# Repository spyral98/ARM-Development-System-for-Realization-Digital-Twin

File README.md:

# ARM-Development-System-to-Support-Digital-Twin-of-Stepper-Motor 
This repository consists of the work conducted for the thesis "ARM Development System to Support Digital Twin of Stepper Motor". It contains all the files necessary for the development of a fully functional system built around an STM32 Cortex-M4 microcontroller, as well as the code for a demo application for it. It also contains the code for a data representation application using Matlab.

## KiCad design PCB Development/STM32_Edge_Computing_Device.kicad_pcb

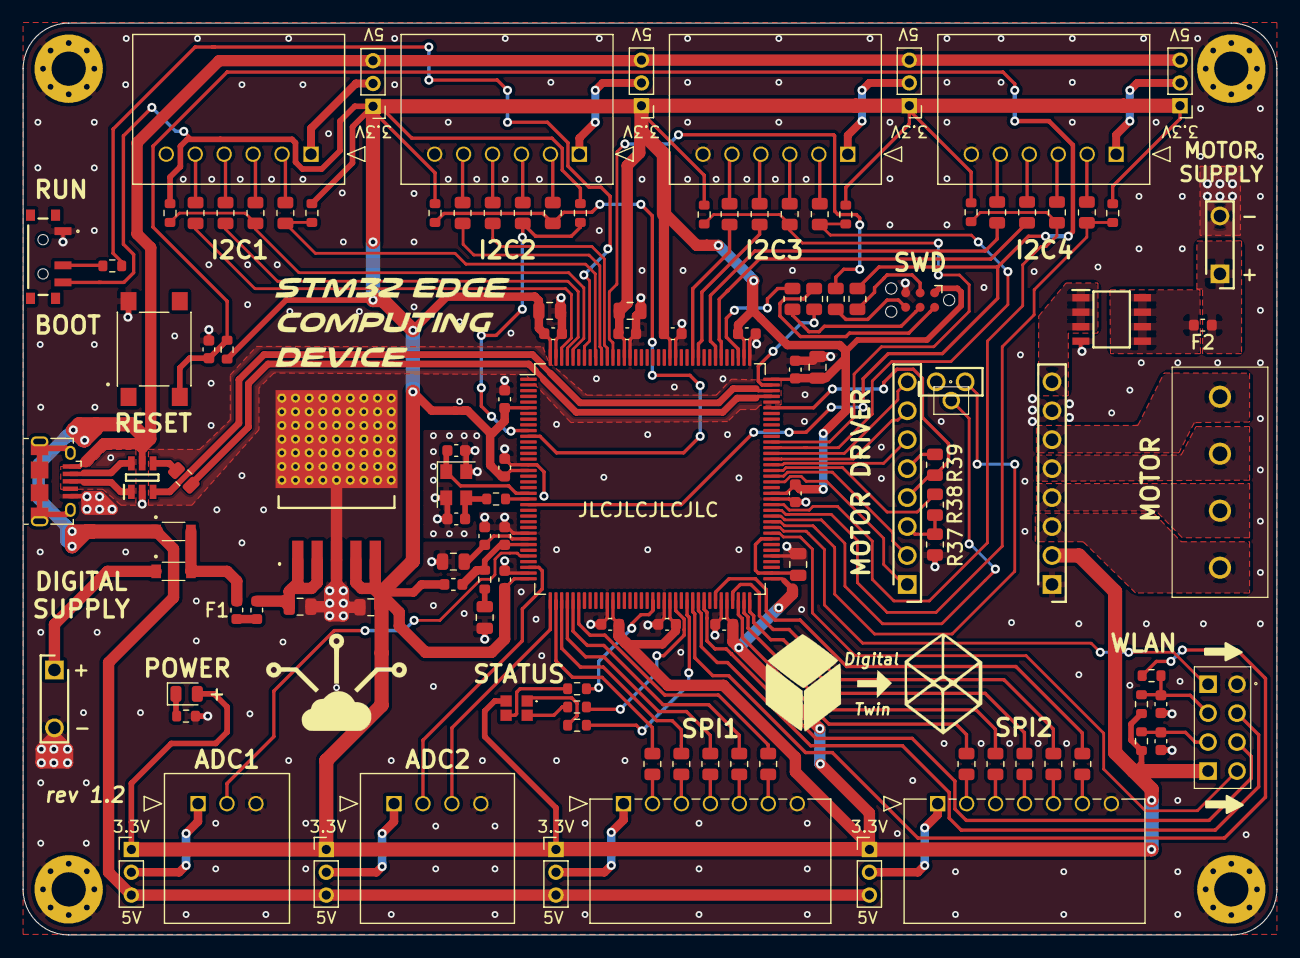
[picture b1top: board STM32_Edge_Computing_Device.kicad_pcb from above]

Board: 2 copper layers, 110.0 x 80.0 mm, 125 parts (0 on the bottom side), 124 nets.

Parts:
C1, C2: 10u; C_0805_2012Metric
C3: 2.2u; C_0805_2012Metric
C4, C6, C10, C11, C12, C13, C14, C15, C16, C17, C18, C19, C20, C21, C27, C28: 100n; C_0603_1608Metric
C5, C9, C23: 1u; C_0805_2012Metric
C7, C8: 4.7u; C_0805_2012Metric
C24: 10n; C_0603_1608Metric
C25, C26: 15p; C_0603_1608Metric
D1, D2: RSX101MM-30TFTR; RSX101MM30TFTR
D3: AP2012MGC; LED_0805_2012Metric
D4: SML-LXT0805SIUGUBW; SMLLXT0805SIUGUBW
F1: SF-0603HIA100M-2; Fuse_0603_1608Metric
F2: SF-0603HIA300M-2; Fuse_0603_1608Metric
FB1, FB2: FBTH1608HE101-T; L_0603_1608Metric
H1, H2, H3, H4: MountingHole_Pad; MountingHole_3mm_Pad_Via
J1, J3: TSW-202-07-F-S; HDRV2W64P254X508_1X2_762X241X838P
J2: 10118194-0001LF; USB_Micro-B_Amphenol_10118194_Horizontal
J4: Conn_ARM_JTAG_SWD_6; Tag-Connect_TC2030-IDC-NL_2x03_P1.27mm_Vertical
J5, J6, J7, J8: 90136-2106; 901362106
J9: 1935187
J10, J11: SSQ-108-01-F-S; RHDR8W64P254_1X8_2083X241X851P
J12: SSQ-101-01-T-S; SSQ-101-XX-YYY-S
J13: SSQ-102-01-T-S; RHDR2W64P254_1X2_559X241X851P
J14, J15: 90136-2107; 901362107
J16: SSQ-104-01-L-D; SSQ-104-XX-YYY-D
J17: 90136-2103; 901362103
J18: 90136-2104; 901362104
JP1, JP2, JP3, JP4, JP5, JP6, JP7, JP8: 2SN-BK-G; PinHeader_1x03_P2.00mm_Vertical
R0, R37, R38, R39: 0; R_0805_2012Metric
R1, R13, R14, R15: 1k; R_0603_1608Metric
R2, R16, R51, R52: 10k; R_0603_1608Metric
R3: 2; R_0603_1608Metric
R4, R5, R6, R7, R8, R9, R10, R11: 4.7k; R_0603_1608Metric
R12: 910; R_0603_1608Metric
R17, R18, R19, R20, R21, R22, R23, R24, R25, R26, R27, R28, R29, R30, R31, R32, R33, R34, R35, R36, R40, R41, R42, R43, R44, R45, R46, R47, R48, R49: 22; R_0805_2012Metric
R50: 330; R_0603_1608Metric
SW1: DTSZML-62K-V-T/R; SW_Push_1P1T_NO_6x6mm_H4.5mm
SW2: SSSS811101
U1: TL1963A-33KTTR; TL1963A33KTTR
U2: CM1231-02SO; SOT95P280X145-6N
U3: DMPH4015SSS-13; SOIC127P600X170-8N
U4: STM32L4S9ZIT6; LQFP-144_20x20mm_P0.5mm
XTAL1: 7M-12.000MEHE-T; Crystal_SMD_3225-4Pin_3.2x2.5mm_custom

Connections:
+3.3VA: C24.1, FB2.2, R3.1, U4.30
+3V3: C2.1, C7.1, C8.1, C9.1, C10.1, C11.1, C12.1, C13.1, C14.1, C15.1, C16.1, C17.1, C18.1, C19.1, C20.1, C21.1, D3.2, D4.2, FB2.1, J4.1, J10.2, J16.8, JP1.1, JP2.1, JP3.1, JP4.1, JP5.1, JP6.1, JP7.1, JP8.1, R2.1, R4.1, R5.1, R6.1, R7.1, R8.1, R9.1, R10.1, R11.1, R51.1, R52.1, SW2.3, U1.4, U1.5, U4.6, U4.17, U4.36, U4.48, U4.58, U4.68, U4.73, U4.88, U4.108, U4.110, U4.123, U4.131, U4.144
+5V: D1.2, J2.1, JP1.3, JP2.3, JP3.3, JP4.3, JP5.3, JP6.3, JP7.3, JP8.3, U2.5
/IO Connectors/1A: J9.2, J10.4
/IO Connectors/1B: J9.1, J10.3
/IO Connectors/2A: J9.3, J10.5
/IO Connectors/2B: J9.4, J10.6
/Power/USB_CONN_D+: J2.3, U2.1
/Power/USB_CONN_D-: J2.2, U2.6
BOOT0: R16.1, U4.138
CUR_SENS: J17.2, U4.32
ESP_EN: R50.2, U4.62
ESP_GPIO0: J16.5, U4.64
ESP_GPIO2: J16.3, U4.63
ESP_RX: J16.7, U4.81
ESP_TX: J16.2, U4.82
GND: C1.2, C2.2, C3.2, C4.2, C5.2, C6.2, C7.2, C8.2, C9.2, C10.2, C11.2, C12.2, C13.2, C14.2, C15.2, C16.2, C17.2, C18.2, C19.2, C20.2, C21.2, C23.2, C24.2, C25.2, C26.2, C27.2, C28.2, H1.1, H2.1, H3.1, H4.1, J1.2, J2.5, J3.2, J4.5, J5.6, J6.6, J7.6, J8.6, J10.1, J10.7, J14.7, J15.7, J16.1, J17.3, J18.4, R1.2, R37.1, SW1.2, SW2.1, U1.3, U1.6, U2.2, U3.4, U4.16, U4.28, U4.35, U4.47, U4.57, U4.67, U4.77, U4.87, U4.109, U4.122, U4.130, U4.143, XTAL1.2, XTAL1.4
HSE_IN: C25.1, U4.21, XTAL1.1
HSE_OUT: R12.1, U4.22
I2C1_AD0: R23.2, U4.141
I2C1_INT: R24.2, U4.142
I2C1_SCL: R5.2, R21.2, U4.136
I2C1_SDA: R4.2, R22.2, U4.140
I2C2_AD0: R27.2, U4.134
I2C2_INT: R28.2, U4.135
I2C2_SCL: R7.2, R25.2, U4.11
I2C2_SDA: R6.2, R26.2, U4.10
I2C3_AD0: R31.2, U4.118
I2C3_INT: R32.2, U4.119
I2C3_SCL: R9.2, R29.2, U4.96
I2C3_SDA: R8.2, R30.2, U4.97
I2C4_AD0: R35.2, U4.114
I2C4_INT: R36.2, U4.115
I2C4_SCL: R11.2, R33.2, U4.85
I2C4_SDA: R10.2, R34.2, U4.86
LED_B: R15.2, U4.61
LED_G: R14.2, U4.59
LED_R: R13.2, U4.55
MD_CLK: R38.2, U4.92
MD_DIAG: J13.2, U4.83
MD_DIR: J11.1, U4.90
MD_INDEX: J12.1, U4.84
MD_MS1: J11.7, U4.94
MD_MS2: J11.6, U4.93
MD_NEN: J11.8, U4.95
MD_STEP: J11.2, U4.91
MD_UART: J11.4, R39.2, U4.103
MIC_SENS: J18.2, U4.34
MIC_TH: J18.3, U4.37
NRST: C4.1, R2.2, R17.2, SW1.3, U4.23
unnamed: C1.1, FB1.1, U1.1, U1.2
unnamed: C5.1, C6.1, U4.29
unnamed: C23.1, R3.2
unnamed: C26.1, R12.2, XTAL1.3
unnamed: C27.1, J16.4, R50.1, R51.2
unnamed: C28.1, J16.6, R52.2
unnamed: D1.1, D2.1, F1.1
unnamed: D2.2, J1.1
unnamed: D3.1, R1.1
unnamed: D4.1, R15.1
unnamed: D4.3, R13.1
unnamed: D4.4, R14.1
unnamed: F1.2, FB1.2
unnamed: F2.1, J3.1
unnamed: F2.2, U3.5, U3.6, U3.7, U3.8
unnamed: J4.2, R18.1
unnamed: J4.3, R17.1
unnamed: J4.4, R19.1
unnamed: J4.6, R20.1
unnamed: J5.1, JP1.2
unnamed: J5.2, R21.1
unnamed: J5.3, R22.1
unnamed: J5.4, R23.1
unnamed: J5.5, R24.1
unnamed: J6.1, JP2.2
unnamed: J6.2, R25.1
unnamed: J6.3, R26.1
unnamed: J6.4, R27.1
unnamed: J6.5, R28.1
unnamed: J7.1, JP3.2
unnamed: J7.2, R29.1
unnamed: J7.3, R30.1
unnamed: J7.4, R31.1
unnamed: J7.5, R32.1
unnamed: J8.1, JP4.2
unnamed: J8.2, R33.1
unnamed: J8.3, R34.1
unnamed: J8.4, R35.1
unnamed: J8.5, R36.1
unnamed: J11.3, R37.2, R38.1
unnamed: J11.5, R39.1
unnamed: J14.1, JP5.2
unnamed: J14.2, R40.1
unnamed: J14.3, R41.1
unnamed: J14.4, R42.1
unnamed: J14.5, R43.1
unnamed: J14.6, R44.1
unnamed: J15.1, JP6.2
unnamed: J15.2, R45.1
unnamed: J15.3, R46.1
unnamed: J15.4, R47.1
unnamed: J15.5, R48.1
unnamed: J15.6, R49.1
unnamed: J17.1, JP7.2
unnamed: J18.1, JP8.2
unnamed: R0.2, U2.4
unnamed: R16.2, SW2.2
SPI1_CS: R43.2, U4.41
SPI1_INT: R44.2, U4.42
SPI1_MISO: R41.2, U4.39
SPI1_MOSI: R42.2, U4.40
SPI1_SCK: R40.2, U4.38
SPI2_CS: R48.2, U4.69
SPI2_INT: R49.2, U4.66
SPI2_MISO: R46.2, U4.71
SPI2_MOSI: R47.2, U4.72
SPI2_SCK: R45.2, U4.70
SWCLK: R19.2, U4.111
SWDIO: R18.2, U4.107
SWO: R20.2, U4.133
USB_D+: U2.3, U4.106
USB_D-: R0.1, U4.105
VCAPDSI: C3.1, U4.74, U4.80
Vdrive: J10.8, U3.1, U3.2, U3.3

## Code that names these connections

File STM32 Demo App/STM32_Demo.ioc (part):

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Mcu.Name=STM32L4S9ZITx
Mcu.Package=LQFP144
Mcu.UserName=STM32L4S9ZITx
PA1.GPIOParameters=GPIO_Label
PA1.GPIO_Label=CUR_SENS
PA1.Signal=ADCx_IN6
PA11.Mode=Device_Only
PA11.Signal=USB_OTG_FS_DM
PA12.Mode=Device_Only
PA12.Signal=USB_OTG_FS_DP
PA13\ (JTMS/SWDIO).Mode=Trace_Asynchronous_SW
PA13\ (JTMS/SWDIO).Signal=SYS_JTMS-SWDIO
PA14\ (JTCK/SWCLK).Mode=Trace_Asynchronous_SW
PA14\ (JTCK/SWCLK).Signal=SYS_JTCK-SWCLK
PA3.GPIOParameters=GPIO_Label
PA3.GPIO_Label=MIC_SENS
PA3.Signal=ADCx_IN8
PA4.GPIOParameters=GPIO_Label
PA4.GPIO_Label=MIC_TH
PA4.Signal=GPIO_Input
PB3\ (JTDO/TRACESWO).Mode=Trace_Asynchronous_SW
PB3\ (JTDO/TRACESWO).Signal=SYS_JTDO-SWO
PB4\ (NJTRST).GPIOParameters=GPIO_Label
PB4\ (NJTRST).GPIO_Label=I2C2_AD0
PB4\ (NJTRST).Signal=GPIO_Input
PB5.GPIOParameters=GPIO_PuPd,GPIO_Label
PB5.GPIO_Label=I2C2_INT
PB5.GPIO_PuPd=GPIO_PULLDOWN
PB5.Signal=GPXTI5
PB6.Mode=I2C
PB6.Signal=I2C1_SCL
PB9.Mode=I2C
PB9.Signal=I2C1_SDA
PD10.GPIOParameters=GPIO_Label
PD10.GPIO_Label=MD_DIAG
PD10.Signal=GPIO_Input
PD11.GPIOParameters=GPIO_Label
PD11.GPIO_Label=MD_INDEX
PD11.Signal=GPIO_Input
PD12.Signal=I2C4_SCL
PD13.Signal=I2C4_SDA
PD15.GPIOParameters=PinState,GPIO_Label
PD15.GPIO_Label=MD_DIR
PD15.PinState=GPIO_PIN_SET
PD15.Signal=GPIO_Output
PD8.Mode=Asynchronous
PD8.Signal=USART3_TX
PD9.Mode=Asynchronous
PD9.Signal=USART3_RX
PE0.GPIOParameters=GPIO_Label
PE0.GPIO_Label=I2C1_AD0
PE0.Signal=GPIO_Input
PE1.GPIOParameters=GPIO_Label
PE1.GPIO_Label=I2C1_INT
PE1.Signal=GPIO_Input
PE10.GPIOParameters=PinState,GPIO_Label
PE10.GPIO_Label=LED_G
PE10.PinState=GPIO_PIN_SET
PE10.Signal=GPIO_Output
PE12.GPIOParameters=PinState,GPIO_Label
PE12.GPIO_Label=LED_B
PE12.PinState=GPIO_PIN_SET
PE12.Signal=GPIO_Output
PE13.GPIOParameters=PinState,GPIO_Label
PE13.GPIO_Label=ESP_EN
PE13.PinState=GPIO_PIN_SET
PE13.Signal=GPIO_Output
PE14.GPIOParameters=PinState,GPIO_PuPd,GPIO_Label,GPIO_ModeDefaultOutputPP
PE14.GPIO_Label=ESP_GPIO1
PE14.GPIO_ModeDefaultOutputPP=GPIO_MODE_OUTPUT_OD
PE14.GPIO_PuPd=GPIO_PULLUP
PE14.PinState=GPIO_PIN_SET
PE14.Signal=GPIO_Output
PE15.GPIOParameters=PinState,GPIO_PuPd,GPIO_Label,GPIO_ModeDefaultOutputPP
PE15.GPIO_Label=ESP_GPIO0
PE15.GPIO_ModeDefaultOutputPP=GPIO_MODE_OUTPUT_OD
PE15.GPIO_PuPd=GPIO_PULLUP
PE15.PinState=GPIO_PIN_SET
PE15.Signal=GPIO_Output
PE8.GPIOParameters=PinState,GPIO_Label
PE8.GPIO_Label=LED_R
PE8.PinState=GPIO_PIN_SET
PE8.Signal=GPIO_Output
PF0.GPIOParameters=GPIO_Speed,GPIO_Pu
PF0.GPIO_Pu=GPIO_PULLUP
PF0.GPIO_Speed=GPIO_SPEED_FREQ_MEDIUM
PF0.Mode=I2C
PF0.Signal=I2C2_SDA
PF1.GPIOParameters=GPIO_Speed,GPIO_Pu
PF1.GPIO_Pu=GPIO_PULLUP
PF1.GPIO_Speed=GPIO_SPEED_FREQ_MEDIUM
PF1.Mode=I2C
PF1.Signal=I2C2_SCL
PG2.GPIOParameters=GPIO_Label
PG2.GPIO_Label=MD_STEP
PG2.Signal=GPIO_Output
PG4.GPIOParameters=PinState,GPIO_Label
PG4.GPIO_Label=MD_MS2
PG4.PinState=GPIO_PIN_SET
PG4.Signal=GPIO_Output
PG5.GPIOParameters=PinState,GPIO_Label
PG5.GPIO_Label=MD_MS1
PG5.PinState=GPIO_PIN_SET
PG5.Signal=GPIO_Output
PG6.GPIOParameters=PinState,GPIO_Label,GPIO_ModeDefaultOutputPP
PG6.GPIO_Label=MD_NEN
PG6.GPIO_ModeDefaultOutputPP=GPIO_MODE_OUTPUT_OD
PG6.PinState=GPIO_PIN_SET
PG6.Signal=GPIO_Output
PG7.Mode=I2C
PG7.Signal=I2C3_SCL
PG8.Mode=I2C
PG8.Signal=I2C3_SDA
PH0-OSC_IN\ (PH0).Mode=HSE-External-Oscillator
PH0-OSC_IN\ (PH0).Signal=RCC_OSC_IN
PH1-OSC_OUT\ (PH1).Mode=HSE-External-Oscillator
PH1-OSC_OUT\ (PH1).Signal=RCC_OSC_OUT
RCC.HSE_VALUE=16000000
RCC.SYSCLKFreq_VALUE=120000000
RCC.SYSCLKSource=RCC_SYSCLKSOURCE_PLLCLK
board=custom

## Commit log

2023-11-17 Adding STM32CubeIDE files
2023-11-17 Fixing Folder Structure
2023-11-17 KiCAD Files
2023-11-17 test
2023-11-17 STM32CubeIDE Files
2024-07-01 Added nyquist freq sample for FFT.

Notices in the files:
parts and their libraries:
Copyright 2021 Accelerated Designs. All rights reserved.
